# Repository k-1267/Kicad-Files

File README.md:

# KiCad Projects (Nixie Tube Boards)

趣味の電子工作として作成した KiCad 基板設計データをまとめたリポジトリです。  
主にニキシー管（IN-18等）に関連する駆動基板およびマウント基板の設計データを格納しています。

---

## 1. Projects Overview

### 1) IN-18_MountingBoard
手に入るもので最大のニキシー管 **IN-18** のマウント基板です。
* **特徴:** 下記の駆動基板（Driving Board）と同サイズで設計しており、スタックして（重ねて）使用することが可能です。
* **必要部品:**
    * ニキシー管 IN-18 ×2
    * ニキシー管用ソケットピン ×28
    * ピンヘッダ (2x6) ×2

### 2) NixieTube_DrivingBoard
ニキシー管用の汎用駆動基板です。
* **制御方式:** 外部マイコン（ESP32やArduino等）と **I2C** で接続。
* **仕組み:** GPIOエキスパンダ **MCP23018** で制御信号を生成し、ニキシー管専用ドライバ **K155ID1** (SN74141互換) に入力して各カソード（数字）を選択・点灯させます。
* **拡張性:** 電流制限抵抗値を調整することで、IN-18 以外の管にも流用可能です。コロン（ネオンランプ）制御用の回路（MPSA42使用）も搭載しています。

---

## 2. Hardware Specifications

| 項目 | 内容 |
| :--- | :--- |
| **Logic Voltage** | 5V (K155ID1の動作電圧) |
| **Anode Voltage** | DC 170V (ニキシー管駆動用高電圧) |
| **Communication** | I2C (Address はADRピンのジャンパ設定により変更可能) |
| **Driver IC** | K155ID1 (Russian Nixie Driver) ×2 |
| **Expander IC** | MCP23018 ×1 |

---

## 3. Bill of Materials (BOM)

### Driving Board 主要部品
* **ICs:**
    * MCP23018 (I/O Expander) ×1
    * K155ID1 (Nixie Driver) ×2
* **Discrete Components:**
    * MPSA42 (高耐圧トランジスタ：コロン制御用) ×4
    * ニキシー管用電流制限抵抗 ×2
    * 各種抵抗（BおよびBE抵抗、プルアップ等）
* **Connectors:**
    * ピンヘッダ (1x3) ×3
    * ジャンパピン ×3

---

## 4. Repository Structure
```text
.
├── IN-18_MountingBoard/       # IN-18マウント基板プロジェクト
│   ├── IN-18_MountingBoard.kicad_pro
│   └── ...
├── NixieTube_DrivingBoard/    # 駆動基板プロジェクト
│   ├── NixieTube_DrivingBoard.kicad_pro
│   └── ...
└── images/                    # 回路図・外観プレビュー画像（※適宜追加）

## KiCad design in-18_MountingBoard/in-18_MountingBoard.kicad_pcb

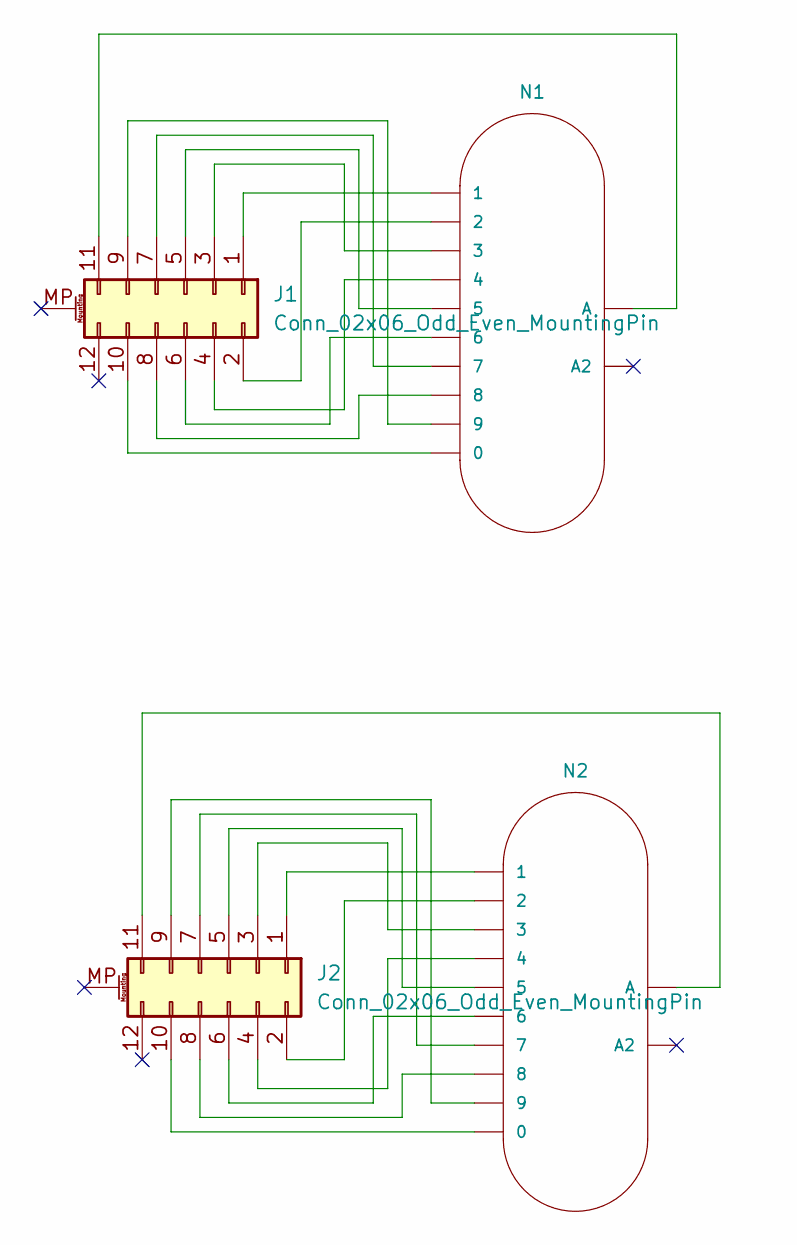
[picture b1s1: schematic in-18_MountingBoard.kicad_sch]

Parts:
J1, J2: Conn_02x06_Odd_Even_MountingPin; PinHeader_2x06_P2.54mm_Horizontal
N1, N2: IN-18; nixies-us-IN-18-DSUB

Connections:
unnamed: J1.1, N1.1
unnamed: J1.2, N1.2
unnamed: J1.3, N1.3
unnamed: J1.4, N1.4
unnamed: J1.5, N1.5
unnamed: J1.6, N1.6
unnamed: J1.7, N1.7
unnamed: J1.8, N1.8
unnamed: J1.9, N1.9
unnamed: J1.10, N1.0
unnamed: J1.11, N1.A
unnamed: J2.1, N2.1
unnamed: J2.2, N2.2
unnamed: J2.3, N2.3
unnamed: J2.4, N2.4
unnamed: J2.5, N2.5
unnamed: J2.6, N2.6
unnamed: J2.7, N2.7
unnamed: J2.8, N2.8
unnamed: J2.9, N2.9
unnamed: J2.10, N2.0
unnamed: J2.11, N2.A

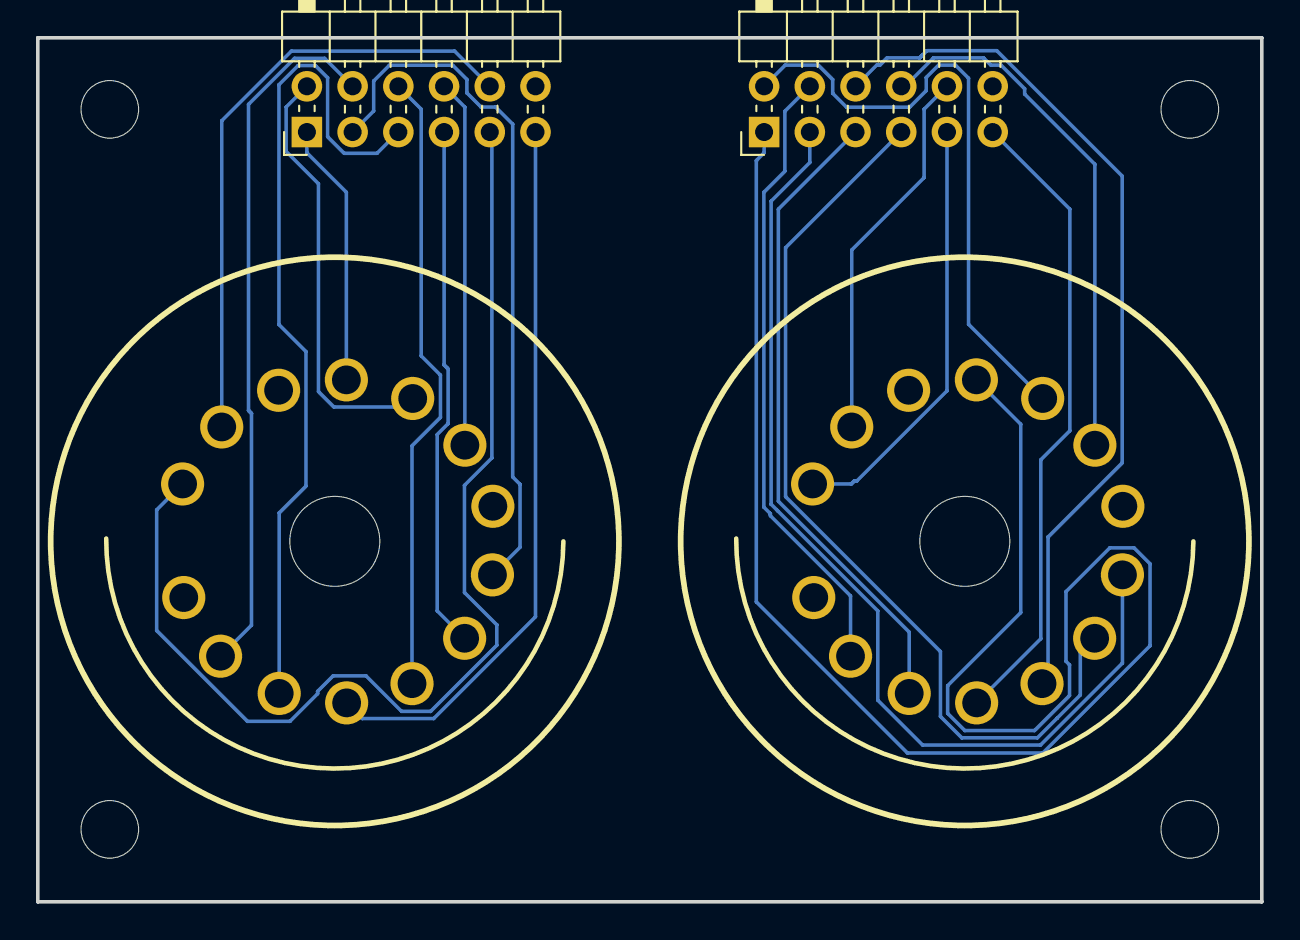
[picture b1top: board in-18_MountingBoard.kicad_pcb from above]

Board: 2 copper layers, 68.0 x 48.0 mm, 8 parts (0 on the bottom side), 22 nets.

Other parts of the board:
REF1, REF2, REF3, REF4: MountingHole_3.2mm_M3

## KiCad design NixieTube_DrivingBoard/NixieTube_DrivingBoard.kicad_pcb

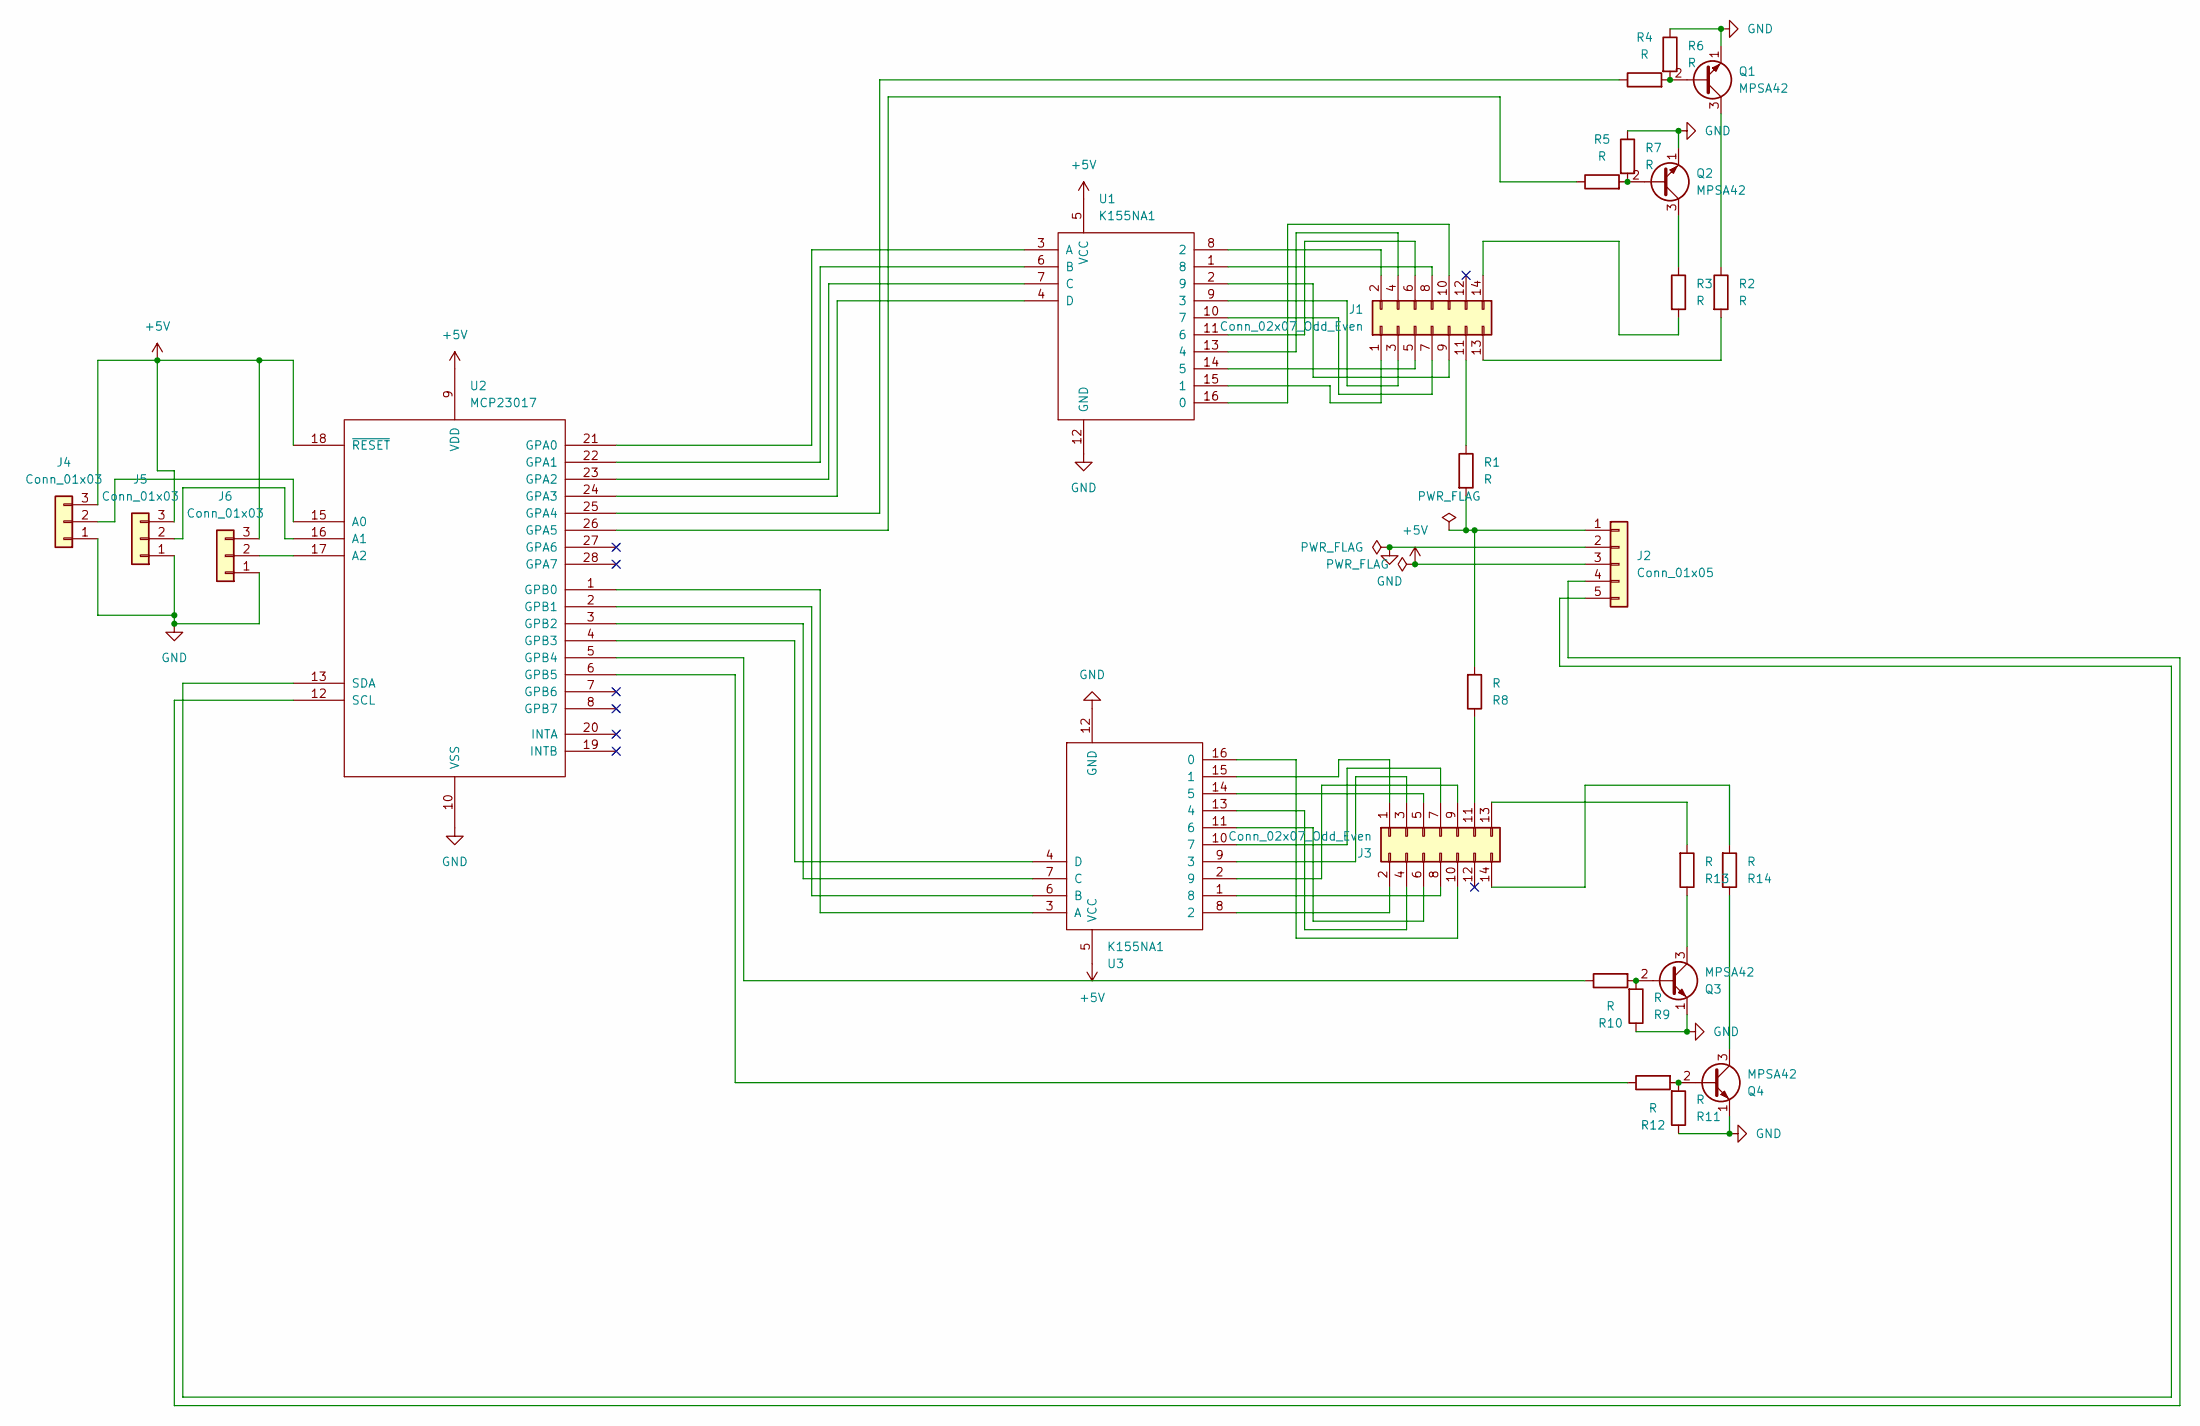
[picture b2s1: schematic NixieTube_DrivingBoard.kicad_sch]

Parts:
J1, J3: Conn_02x07_Odd_Even; PinHeader_2x07_P2.54mm_Vertical
J2: Conn_01x05; PinHeader_1x05_P2.54mm_Vertical
J4, J5, J6: Conn_01x03; PinHeader_1x03_P2.54mm_Vertical
Q1, Q2, Q3, Q4: MPSA42; TO-92_Inline
R1, R2, R3, R4, R5, R6, R7, R8, R9, R10, R11, R12, R13, R14: R; R_Axial_DIN0204_L3.6mm_D1.6mm_P5.08mm_Horizontal
U1, U3: K155NA1; DIP-16_W7.62mm_Socket
U2: MCP23017; DIP-28_W7.62mm_Socket

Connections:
+5V: J2.3, J4.3, J5.3, J6.3, U1.5 (VCC), U2.9 (VDD), U2.18 (~RESET), U3.5 (VCC)
GND: J2.2, J4.1, J5.1, J6.1, Q1.1 (E), Q2.1 (E), Q3.1 (E), Q4.1 (E), R6.1, R7.1, R9.1, R11.1, U1.12 (GND), U2.10 (VSS), U3.12 (GND)
unnamed: J1.1, U1.15 (1)
unnamed: J1.2, U1.8 (2)
unnamed: J1.3, U1.9 (3)
unnamed: J1.4, U1.13 (4)
unnamed: J1.5, U1.14 (5)
unnamed: J1.6, U1.11 (6)
unnamed: J1.7, U1.10 (7)
unnamed: J1.8, U1.1 (8)
unnamed: J1.9, U1.2 (9)
unnamed: J1.10, U1.16 (0)
unnamed: J1.11, R1.1
unnamed: J1.13, R2.2
unnamed: J1.14, R3.2
unnamed: J2.1, R1.2, R8.2
unnamed: J2.4, U2.12 (SCL)
unnamed: J2.5, U2.13 (SDA)
unnamed: J3.1, U3.15 (1)
unnamed: J3.2, U3.8 (2)
unnamed: J3.3, U3.9 (3)
unnamed: J3.4, U3.13 (4)
unnamed: J3.5, U3.14 (5)
unnamed: J3.6, U3.11 (6)
unnamed: J3.7, U3.10 (7)
unnamed: J3.8, U3.1 (8)
unnamed: J3.9, U3.2 (9)
unnamed: J3.10, U3.16 (0)
unnamed: J3.11, R8.1
unnamed: J3.13, R13.2
unnamed: J3.14, R14.2
unnamed: J4.2, U2.15 (A0)
unnamed: J5.2, U2.16 (A1)
unnamed: J6.2, U2.17 (A2)
unnamed: Q1.2 (B), R4.2, R6.2
unnamed: Q1.3 (C), R2.1
unnamed: Q2.2 (B), R5.2, R7.2
unnamed: Q2.3 (C), R3.1
unnamed: Q3.2 (B), R9.2, R10.2
unnamed: Q3.3 (C), R13.1
unnamed: Q4.2 (B), R11.2, R12.2
unnamed: Q4.3 (C), R14.1
unnamed: U1.3 (A), U2.21 (GPA0)
unnamed: U1.6 (B), U2.22 (GPA1)
unnamed: U1.7 (C), U2.23 (GPA2)
unnamed: U1.4 (D), U2.24 (GPA3)
unnamed: R4.1, U2.25 (GPA4)
unnamed: R5.1, U2.26 (GPA5)
unnamed: U2.1 (GPB0), U3.3 (A)
unnamed: U2.2 (GPB1), U3.6 (B)
unnamed: U2.3 (GPB2), U3.7 (C)
unnamed: U2.4 (GPB3), U3.4 (D)
unnamed: R10.1, U2.5 (GPB4)
unnamed: R12.1, U2.6 (GPB5)

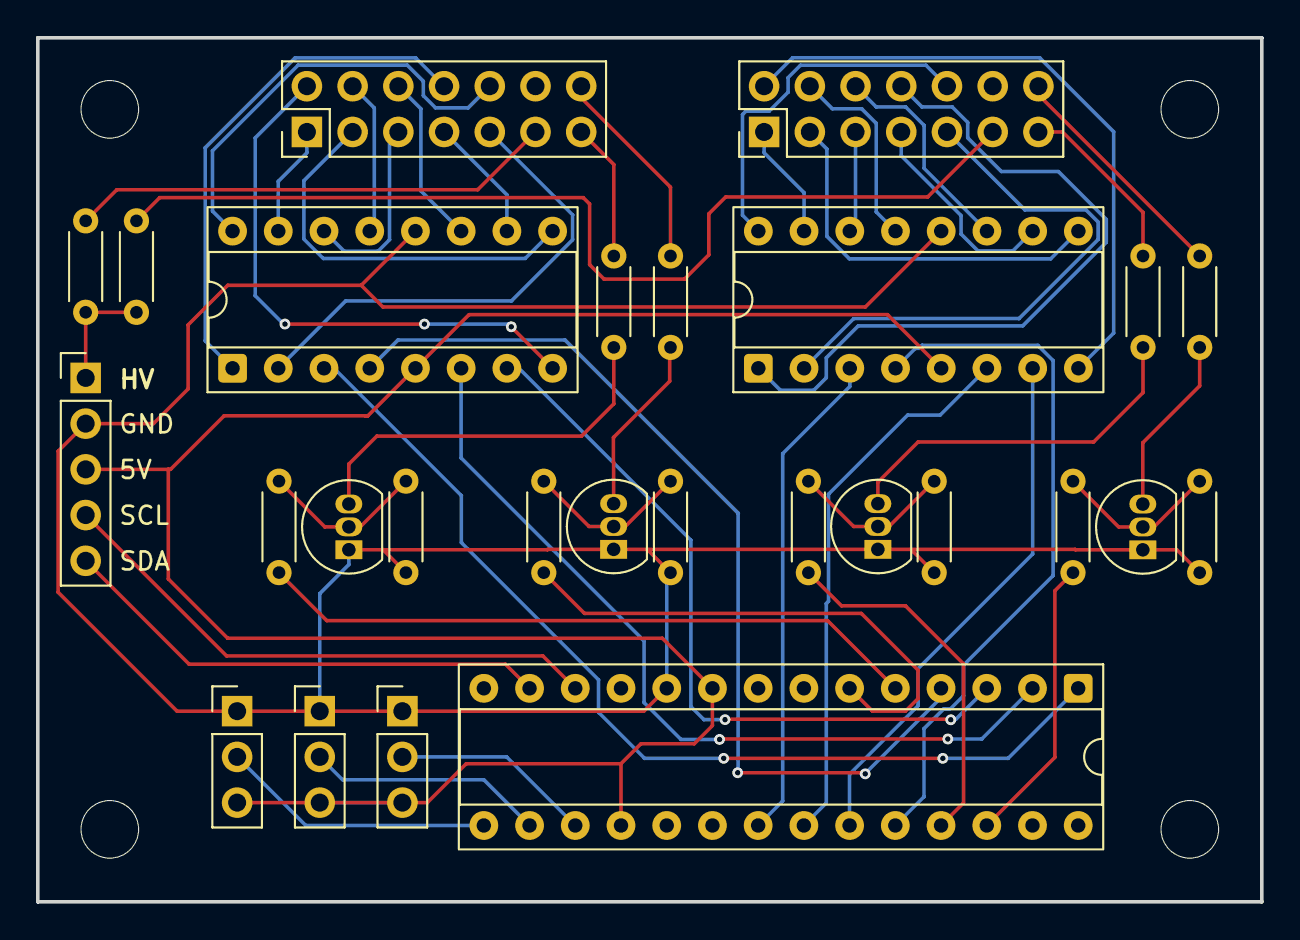
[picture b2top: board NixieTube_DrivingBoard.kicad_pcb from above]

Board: 2 copper layers, 68.0 x 48.0 mm, 31 parts (0 on the bottom side), 54 nets.

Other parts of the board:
REF1, REF2, REF3, REF4: MountingHole_3.2mm_M3

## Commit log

2026-03-04 remove .DS_store
2026-03-04 Remove .DS_Store from repo
2026-03-04 :fix
2026-03-04 Rename foldere
2026-03-17 Improve README.md
